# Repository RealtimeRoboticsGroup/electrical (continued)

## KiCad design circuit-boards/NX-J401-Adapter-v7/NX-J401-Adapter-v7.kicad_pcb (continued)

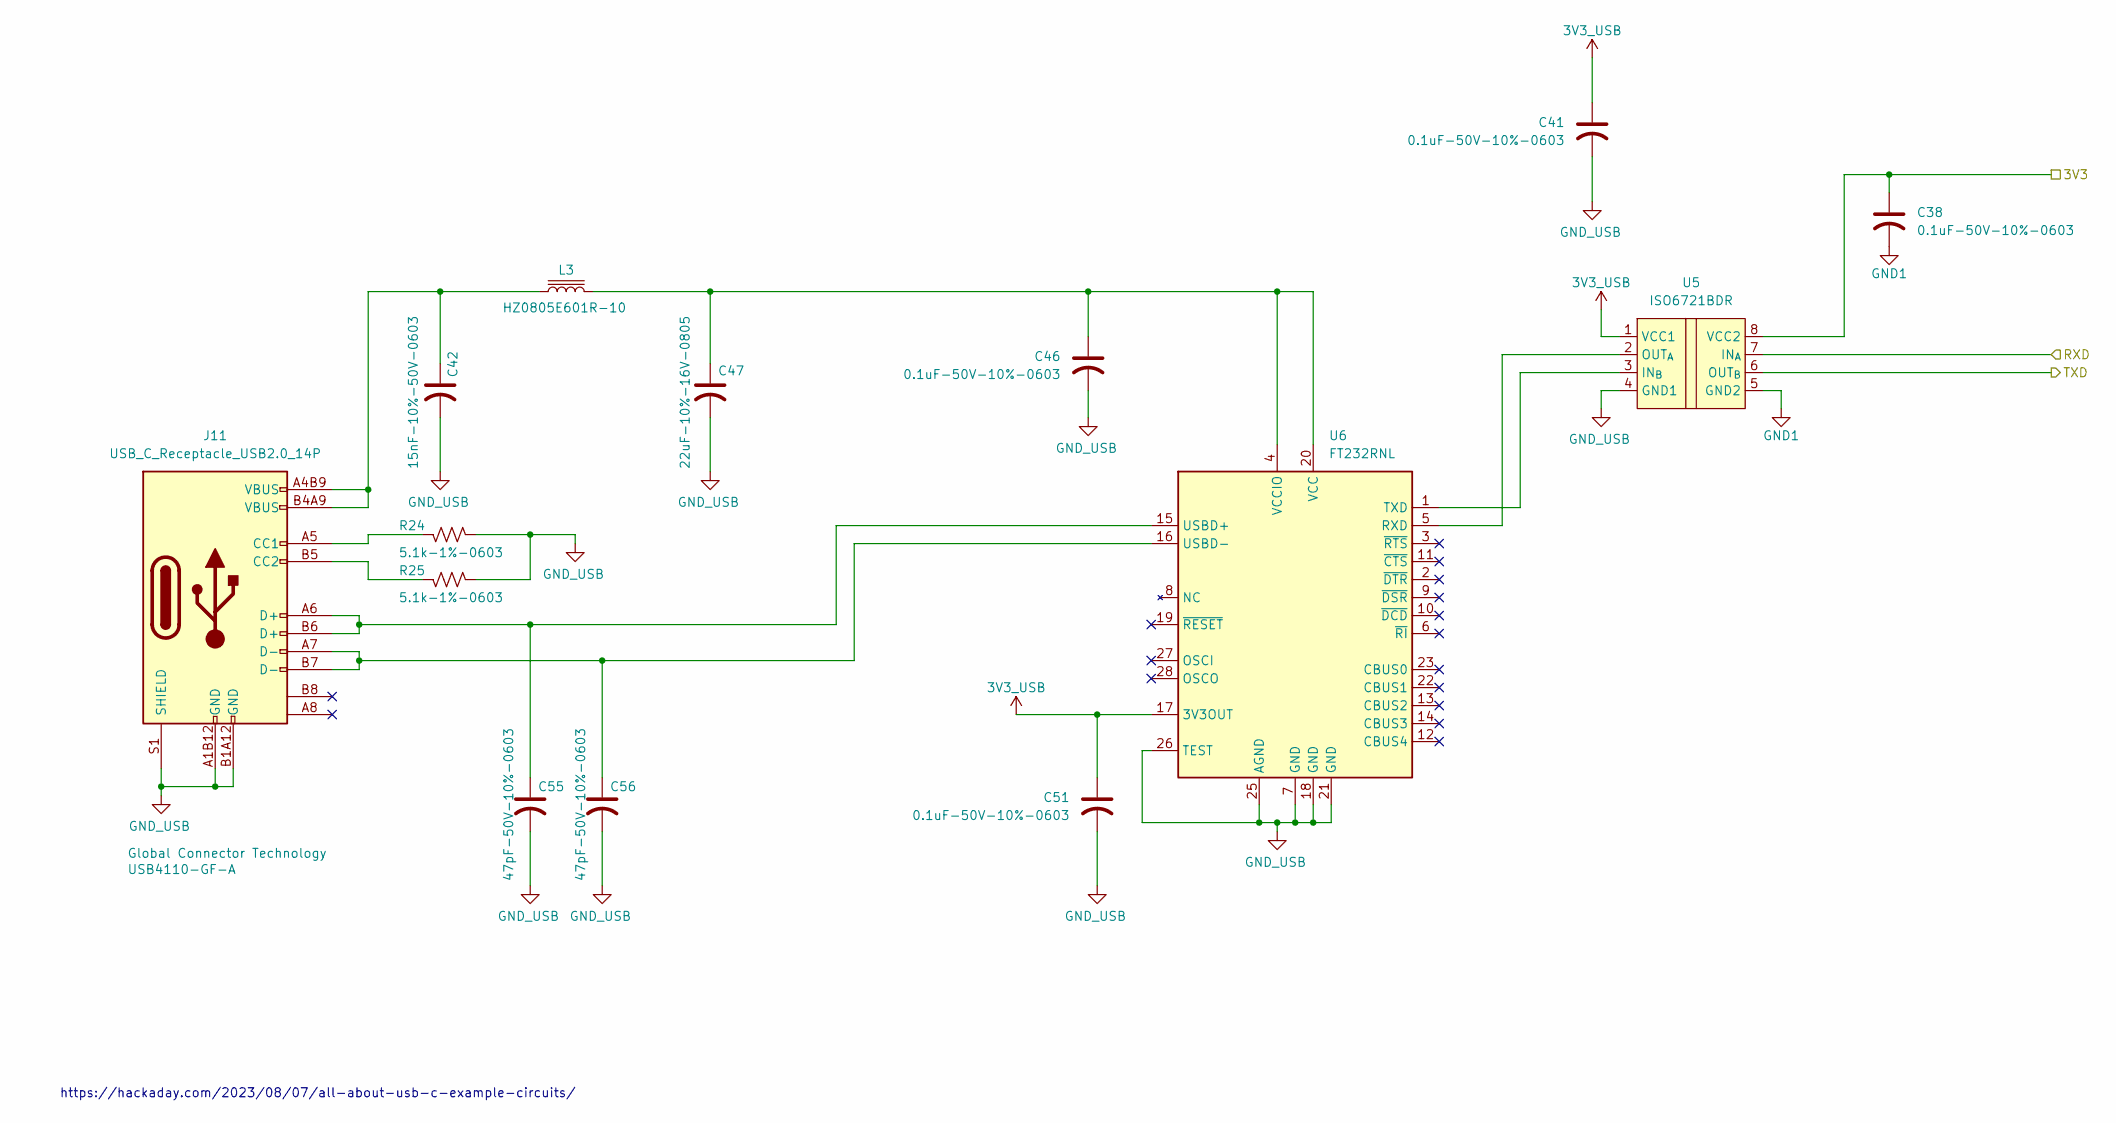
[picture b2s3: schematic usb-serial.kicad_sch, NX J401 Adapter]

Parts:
C38, C41, C46, C51: 0.1uF-50V-10%-0603; C_0603_1608Metric; MFG P/N CC0603KRX7R9BB104; JLCPCB P/N C14663
C42: 15nF-10%-50V-0603; C_0603_1608Metric; MFG P/N CC0603KRX7R9BB153; JLCPCB P/N C107076
C47: 22uF-10%-16V-0805; C_0805_2012Metric; MFG P/N CL21A226KOQNNNE; JLCPCB P/N C296720
C55, C56: 47pF-50V-10%-0603; C_0603_1608Metric; MFG P/N C0603C470K5GACAUTO; JLCPCB P/N C2168903
J11: USB_C_Receptacle_USB2.0_14P; GCT-USB-C-USB4110-GF-A; MFG P/N USB4110-GF-A; JLCPCB P/N C5143397
L3: HZ0805E601R-10; L_0805_2012Metric; MFG P/N HZ0805E601R-10; JLCPCB P/N C2441364
R24, R25: 5.1k-1%-0603; R_0603_1608Metric; MFG P/N RC0603FR-075K1L; JLCPCB P/N C105580
U5: ISO6721BDR; SOIC-8_3.9x4.9mm_P1.27mm; MFG P/N ISO6721BDR; JLCPCB P/N C5216430
U6: FT232RNL; SSOP-28_5.3x10.2mm_P0.65mm; MFG P/N FT232RNL; JLCPCB P/N C8690

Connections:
3V3_USB: C41.1, C51.1, U5.1 (VCC1), U6.17 (3V3OUT)
/3V3_BTN: C38.1, U5.8 (VCC2); also elsewhere on the board
/UART2_RXD: U5.7 (IN_{A}); also elsewhere on the board
/UART2_TXD: U5.6 (OUT_{B}); also elsewhere on the board
GND1: C38.2, U5.5 (GND2); also elsewhere on the board
GND_USB: C41.2, C42.2, C46.2, C47.2, C51.2, C55.2, C56.2, J11.A1B12 (GND), J11.B1A12 (GND), J11.S1 (SHIELD), R24.2, R25.2, U5.4 (GND1), U6.7 (GND), U6.18 (GND), U6.21 (GND), U6.25 (AGND), U6.26 (TEST)
unnamed: C42.1, J11.A4B9 (VBUS), J11.B4A9 (VBUS), L3.1
unnamed: J11.A5 (CC1), R24.1
unnamed: J11.B5 (CC2), R25.1
unnamed: U5.3 (IN_{B}), U6.1 (TXD)
unnamed: U5.2 (OUT_{A}), U6.5 (RXD)
unnamed: C55.1, J11.A6 (D+), J11.B6 (D+), U6.15 (USBD+)
unnamed: C56.1, J11.A7 (D-), J11.B7 (D-), U6.16 (USBD-)
unnamed: C46.1, C47.1, L3.2, U6.4 (VCCIO), U6.20 (VCC)

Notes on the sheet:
https://hackaday.com/2023/08/07/all-about-usb-c-example-circuits/

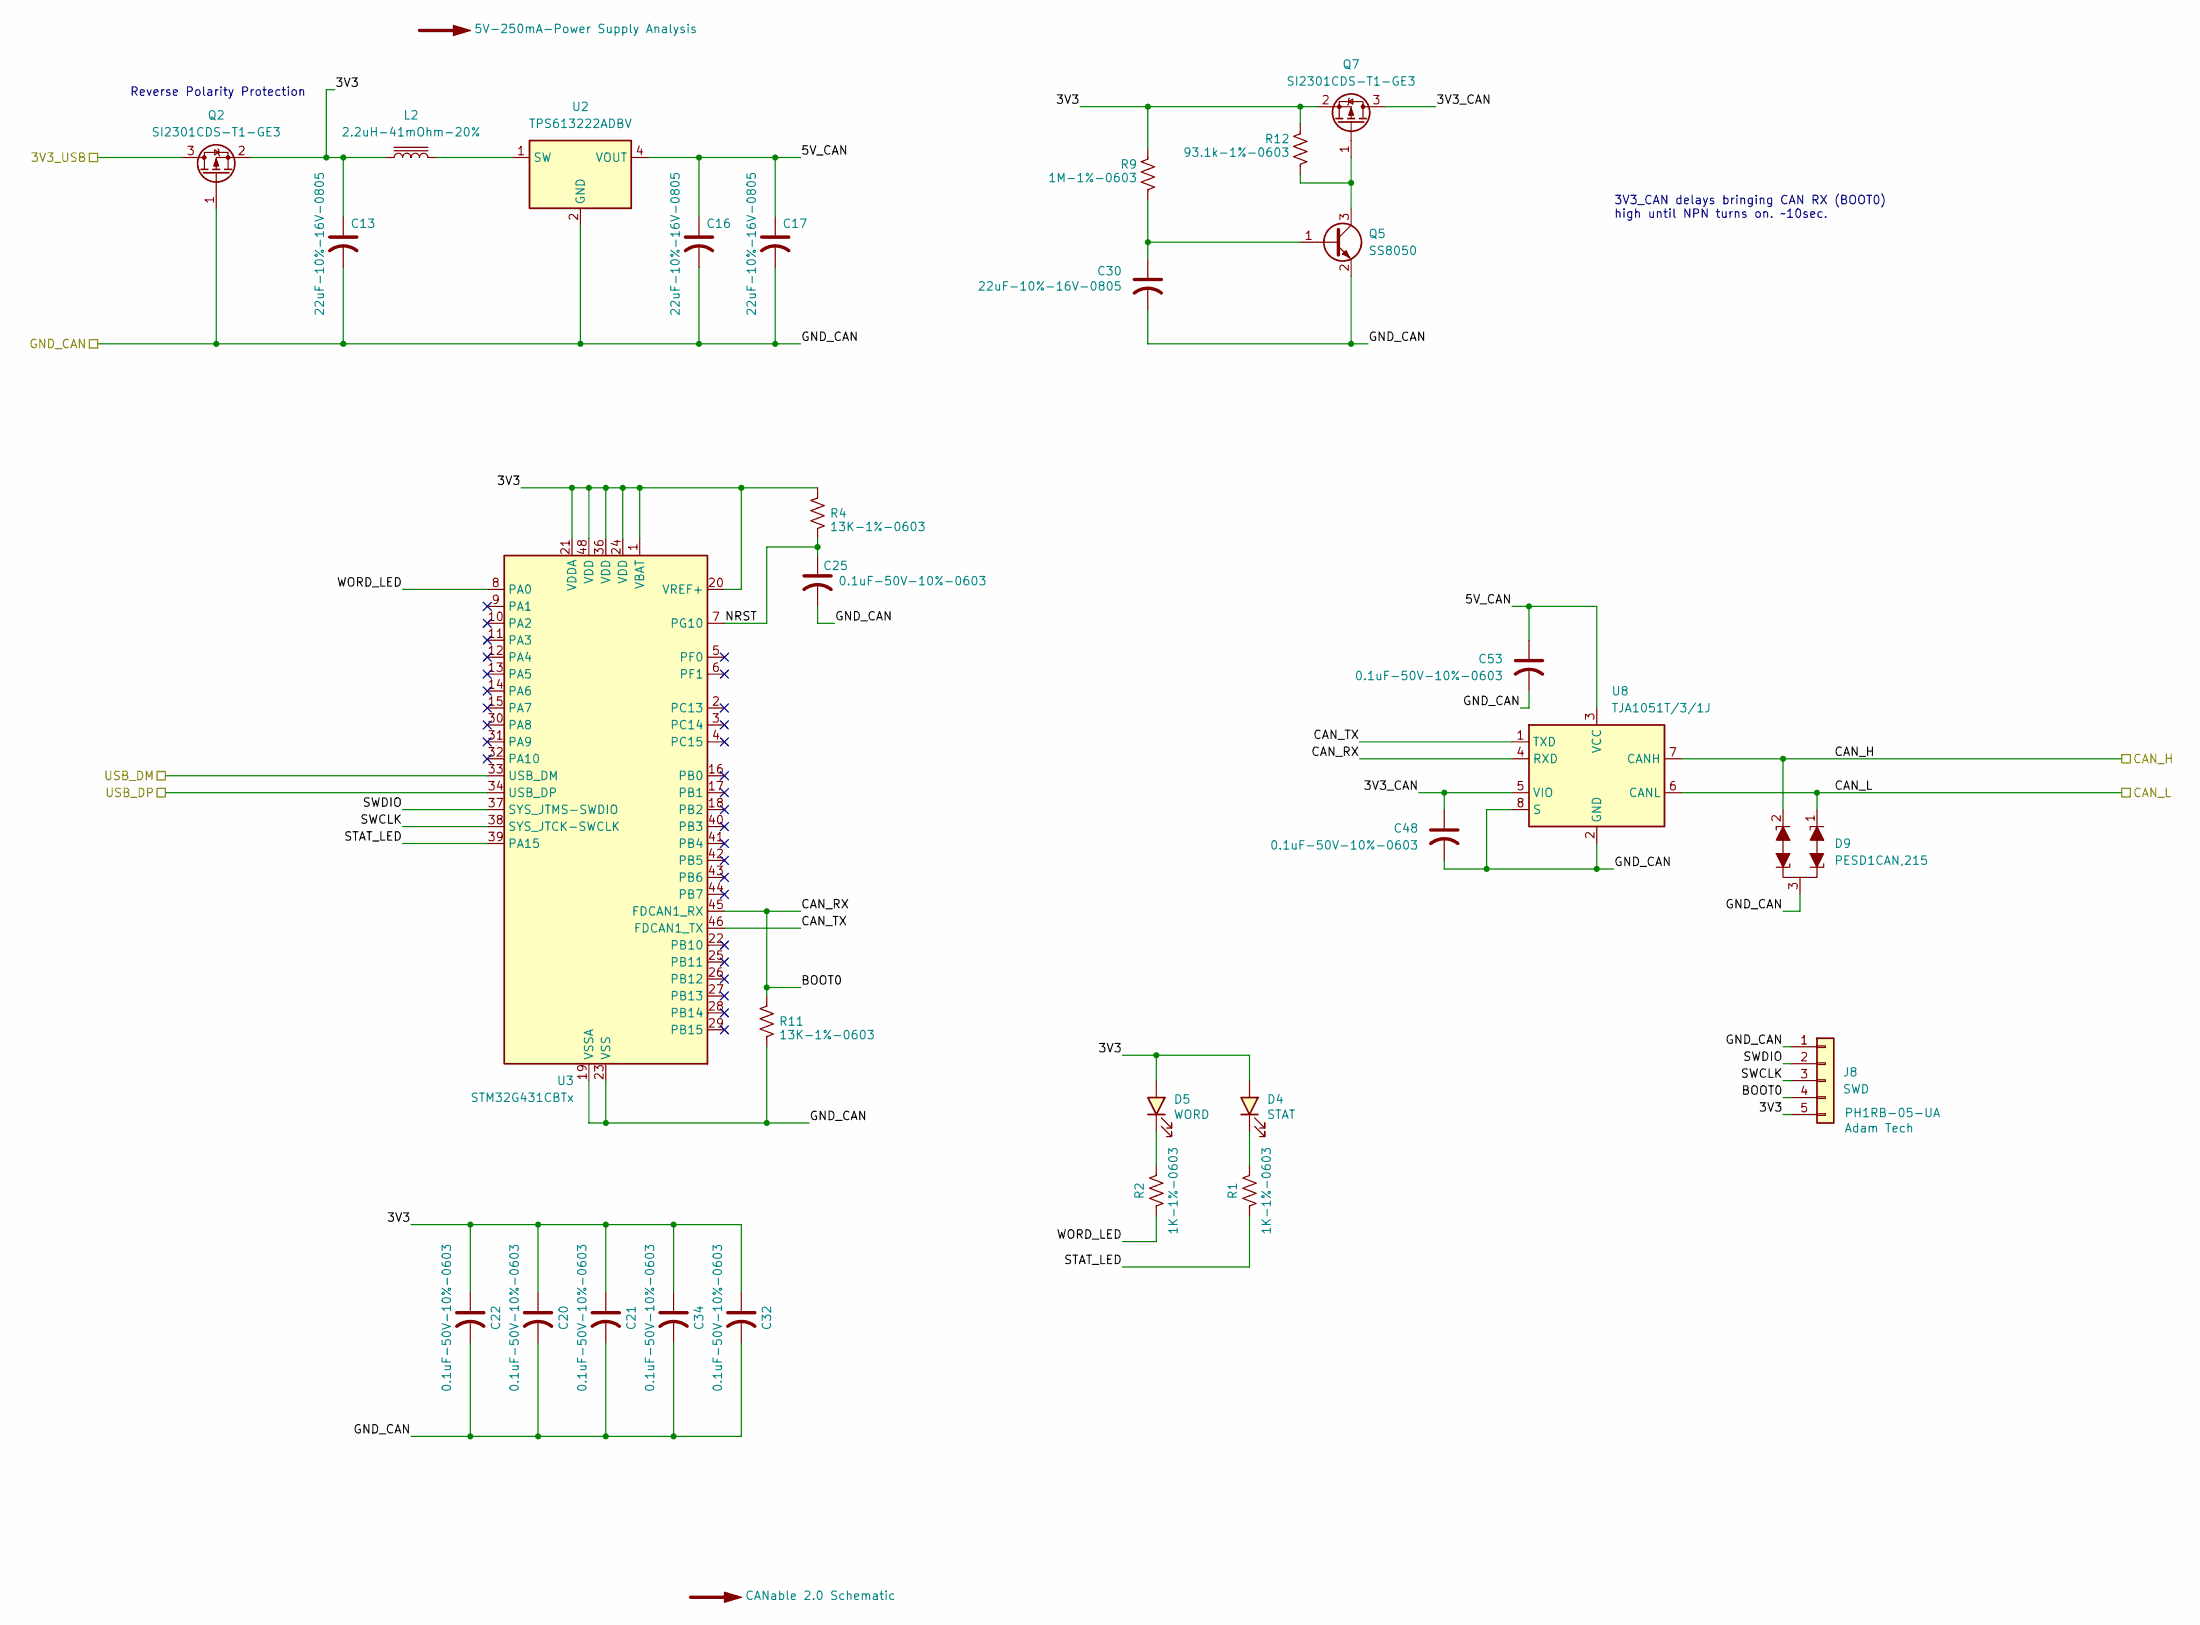
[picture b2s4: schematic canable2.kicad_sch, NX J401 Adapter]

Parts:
C13, C16, C17, C30: 22uF-10%-16V-0805; C_0805_2012Metric; MFG P/N CL21A226KOQNNNE; JLCPCB P/N C296720
C20, C21, C22, C25, C32, C34, C48, C53: 0.1uF-50V-10%-0603; C_0603_1608Metric; MFG P/N CC0603KRX7R9BB104; JLCPCB P/N C14663
D4: STAT; LED_1206_3216Metric; MFG P/N XL-3216UYC; JLCPCB P/N C965824
D5: WORD; LED_1206_3216Metric; MFG P/N XL-3216UYC; JLCPCB P/N C965824
D9: PESD1CAN; SOT-23; MFG P/N PESD1CAN,215; JLCPCB P/N C15771
J8: SWD; PinHeader_1x05_P2.54mm_Horizontal; MFG P/N PH1RB-05-UA; JLCPCB P/N XXXXXX
L2: 2.2uH-41mOhm-20%; KOHER-MDA4020-2R2M; MFG P/N MDA4020-2R2M; JLCPCB P/N C2847469
Q2, Q7: SI2301CDS-T1-GE3; SOT-23; MFG P/N SI2301CDS-T1-GE3; JLCPCB P/N C10487
Q5: SS8050; SOT-23; MFG P/N SS8050(RANGE:200-350); JLCPCB P/N C2150
R1, R2: 1K-1%-0603; R_0603_1608Metric; MFG P/N RC0603FR-071KL; JLCPCB P/N C22548
R4, R11: 13K-1%-0603; R_0603_1608Metric; MFG P/N RC0603FR-0713KL; JLCPCB P/N C137796
R9: 1M-1%-0603; R_0603_1608Metric; MFG P/N RC0603FR-071ML; JLCPCB P/N C105578
R12: 93.1k-1%-0603; R_0603_1608Metric; MFG P/N AC0603FR-0793K1L; JLCPCB P/N C228101
U2: TPS613222ADBV; SOT-23-5; MFG P/N TPS613222ADBVR; JLCPCB P/N C2071163
U3: STM32G431CBTx; LQFP-48_7x7mm_P0.5mm; MFG P/N STM32G431CBT6; JLCPCB P/N C529355
U8: TJA1051T/3/1J; SO-8_3.9x4.9mm_P1.27mm; MFG P/N TJA1051T/3/1J; JLCPCB P/N C38695

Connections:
/CANable2.0/3V3: C13.1, C20.1, C21.1, C22.1, C32.1, C34.1, D4.2 (A), D5.2 (A), J8.5, L2.1, Q2.2 (S), Q7.2 (S), R4.1, R9.1, R12.1, U3.1 (VBAT), U3.20 (VREF+), U3.21 (VDDA), U3.24 (VDD), U3.36 (VDD), U3.48 (VDD)
/CANable2.0/3V3_CAN: C48.1, Q7.3 (D), U8.5 (VIO)
/CANable2.0/3V3_USB: Q2.3 (D); also elsewhere on the board
/CANable2.0/5V_CAN: C16.1, C17.1, C53.1, U2.4 (VOUT), U8.3 (VCC)
/CANable2.0/BOOT0: J8.4, R11.1, U3.45 (FDCAN1_RX), U8.4 (RXD)
/CANable2.0/CAN_H: D9.2 (K1), U8.7 (CANH); also elsewhere on the board
/CANable2.0/CAN_L: D9.1 (K1), U8.6 (CANL); also elsewhere on the board
/CANable2.0/CAN_TX: U3.46 (FDCAN1_TX), U8.1 (TXD)
/CANable2.0/GND_CAN: C13.2, C16.2, C17.2, C20.2, C21.2, C22.2, C25.2, C30.2, C32.2, C34.2, C48.2, C53.2, D9.3 (KK), J8.1, Q2.1 (G), Q5.2 (E), R11.2, U2.2 (GND), U3.19 (VSSA), U3.23 (VSS), U3.35 (VSS), U3.47 (VSS), U8.2 (GND), U8.8 (S); also elsewhere on the board
/CANable2.0/NRST: C25.1, R4.2, U3.7 (PG10)
/CANable2.0/STAT_LED: R1.2, U3.39 (PA15)
/CANable2.0/SWCLK: J8.3, U3.38 (SYS_JTCK-SWCLK)
/CANable2.0/SWDIO: J8.2, U3.37 (SYS_JTMS-SWDIO)
/CANable2.0/USB_DM: U3.33 (USB_DM); also elsewhere on the board
/CANable2.0/USB_DP: U3.34 (USB_DP); also elsewhere on the board
/CANable2.0/WORD_LED: R2.2, U3.8 (PA0)
unnamed: D4.1 (K), R1.1
unnamed: D5.1 (K), R2.1
unnamed: C30.1, Q5.1 (B), R9.2
unnamed: Q5.3 (C), Q7.1 (G), R12.2
unnamed: L2.2, U2.1 (SW)

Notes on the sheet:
3V3_CAN delays bringing CAN RX (BOOT0) high until NPN turns on. ~10sec.
Reverse Polarity Protection

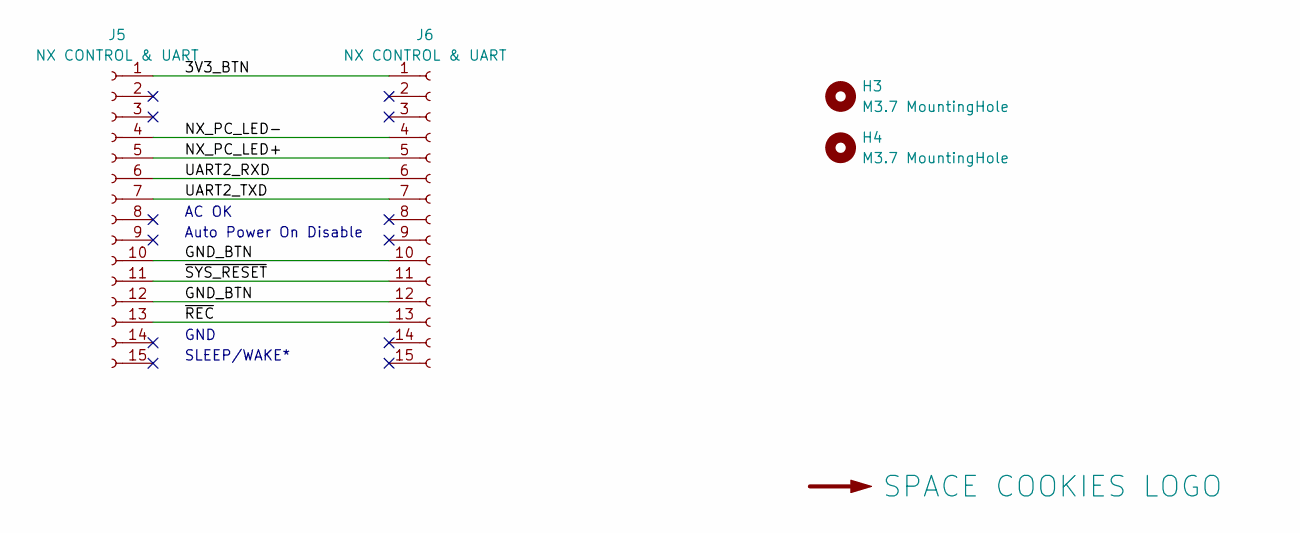
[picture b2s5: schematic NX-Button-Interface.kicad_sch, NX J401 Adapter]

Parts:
H3, H4: M3.7 MountingHole; MountingHole_3.7mm
J5, J6: NX CONTROL & UART; PinSocket_1x15_P2.54mm_Vertical; MFG P/N PPTC151LFBN-RC; JLCPCB P/N XXXXXX
LOGO2: SPACE COOKIES LOGO; SPACE_COOKIES_LOGO_7mm

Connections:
/NX-Button Interface/3V3_BTN: J5.1, J6.1
/NX-Button Interface/GND_BTN: J5.10, J5.12, J6.10, J6.12
/NX-Button Interface/NX_PC_LED+: J5.5, J6.5
/NX-Button Interface/NX_PC_LED-: J5.4, J6.4
/NX-Button Interface/UART2_RXD: J5.6, J6.6
/NX-Button Interface/UART2_TXD: J5.7, J6.7
/NX-Button Interface/~REC: J5.13, J6.13
/NX-Button Interface/~SYS_RESET: J5.11, J6.11

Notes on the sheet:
AC OK
GND
Auto Power On Disable
SLEEP/WAKE*

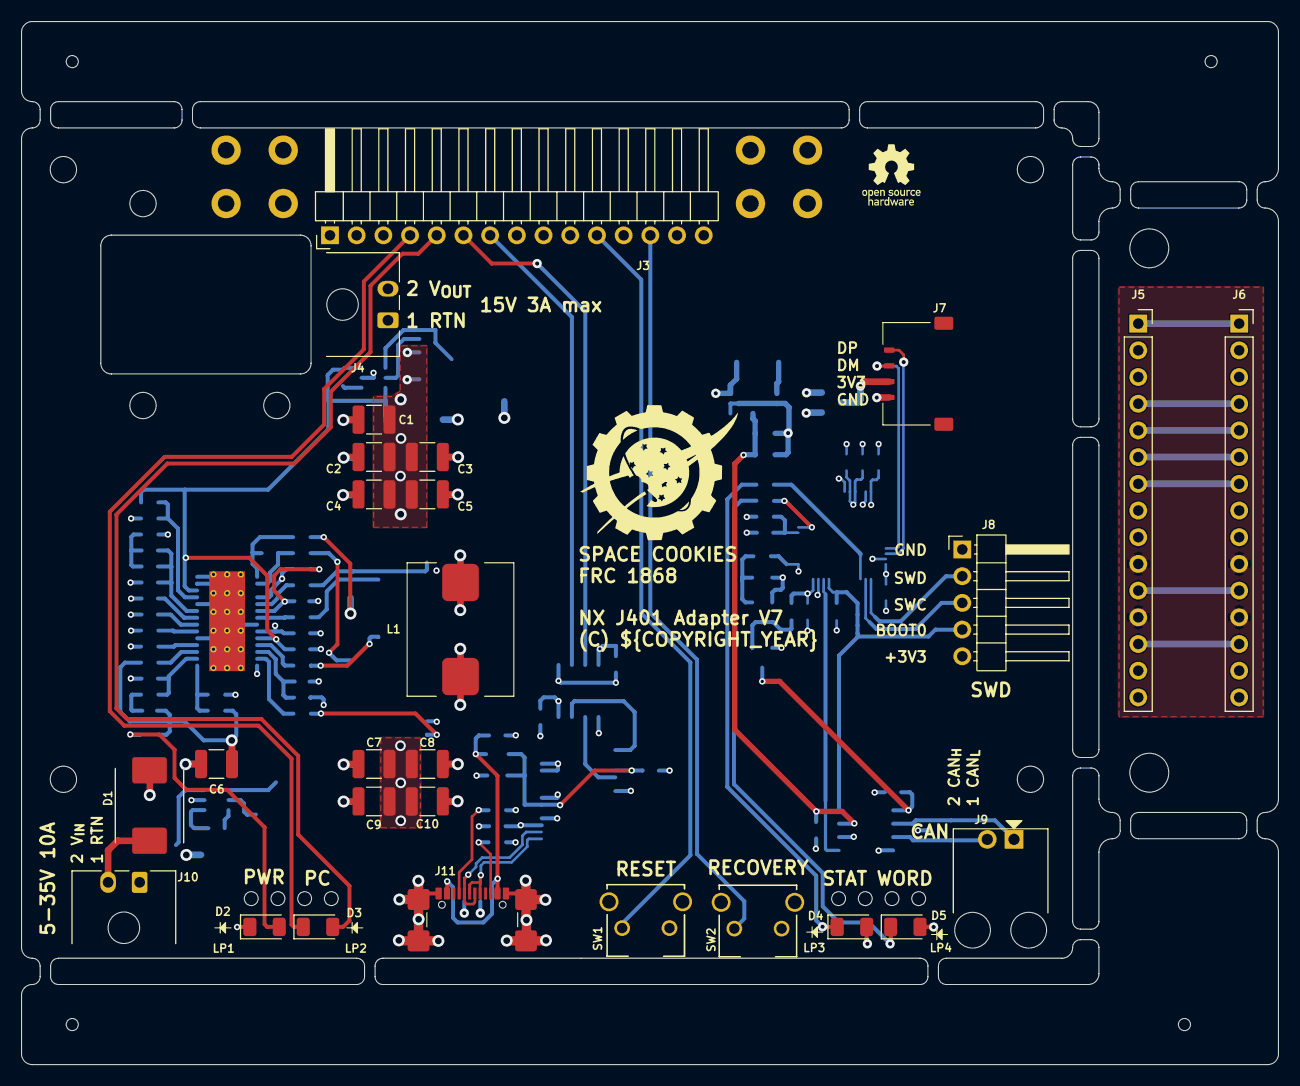
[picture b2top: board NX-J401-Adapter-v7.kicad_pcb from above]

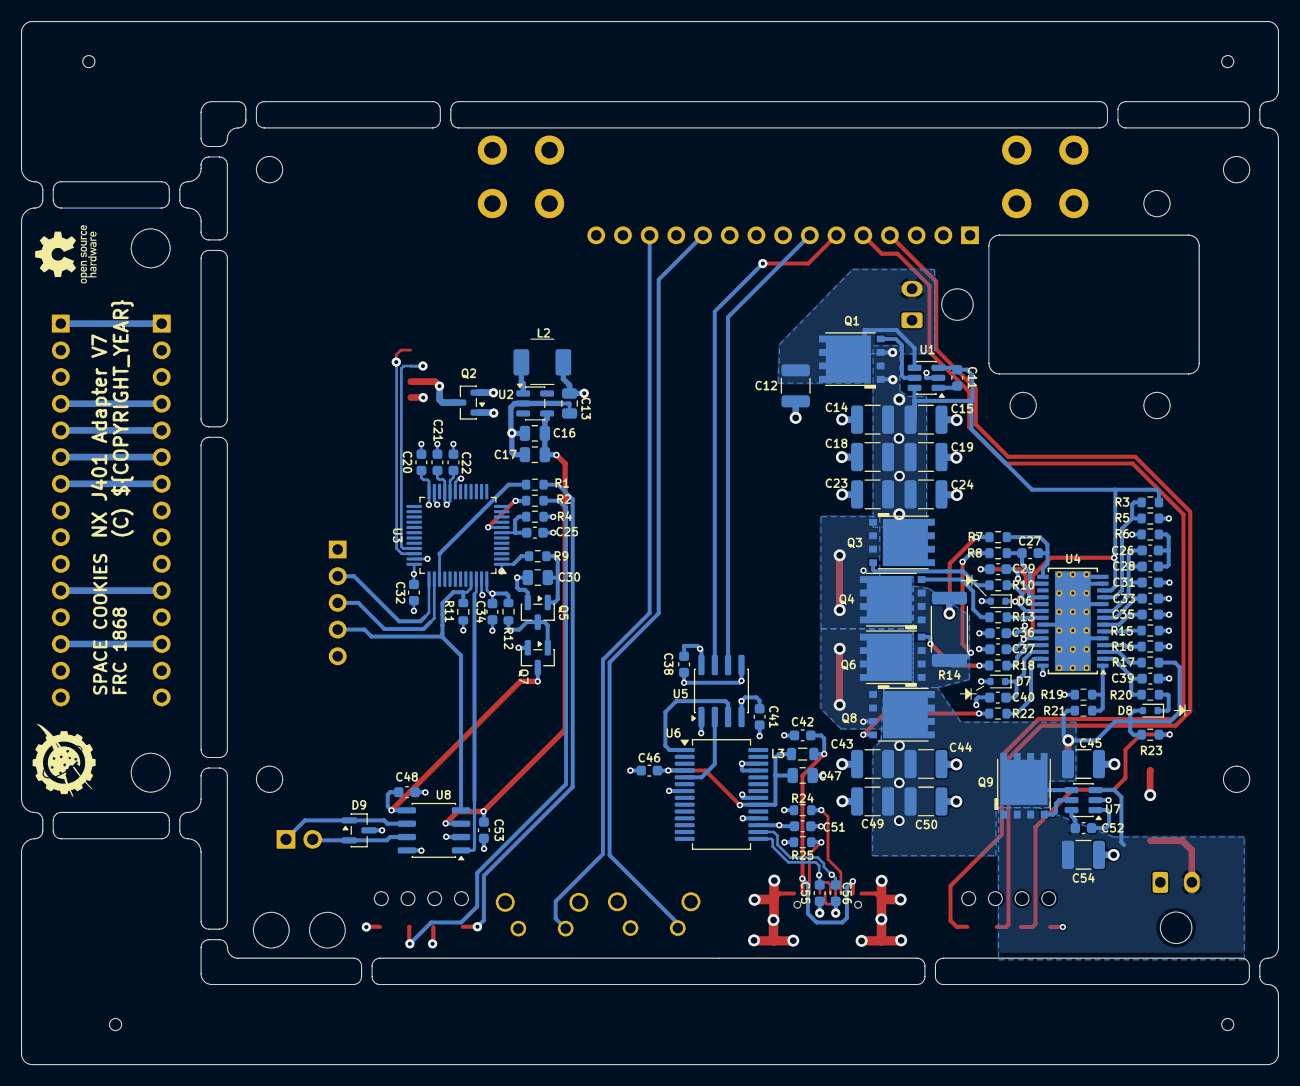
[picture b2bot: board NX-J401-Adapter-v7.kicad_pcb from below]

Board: 4 copper layers, 119.6 x 99.2 mm, 142 parts (95 on the bottom side), 84 nets.

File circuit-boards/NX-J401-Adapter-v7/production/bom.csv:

Designator,Footprint,Quantity,Value,LCSC Part #
"C1, C10, C12, C14, C15, C18, C19, C2, C23, C24, C3, C4, C43, C44, C45, C49, C5, C50, C54, C6, C7, C8, C9",1210,23,10uF-50V-10%-X7R-1210,C77102
"C11, C20, C21, C22, C25, C29, C32, C34, C37, C38, C39, C40, C41, C46, C48, C51, C52, C53",0603,18,0.1uF-50V-10%-0603,C14663
"C13, C16, C17, C30, C47",0805,5,22uF-10%-16V-0805,C296720
"C26, C28",0603,2,5.6nF-10%-50V-0603,C107095
"C27, C55, C56",0603,3,47pF-50V-10%-0603,C2168903
C31,0603,1,270pF-10%-50V-0603,C107084
"C33, C42",0603,2,15nF-10%-50V-0603,C107076
C35,0603,1,150pF-50V-10%-0603,C107075
C36,0603,1,1uF-50V-10%-0603,C105174
D1,D_SMC_Littelfuse_DO-214AB,1,24V,C284061
D2,1206,1,PWR,C5123493
D3,1206,1,PC,C5123493
D4,1206,1,STAT,C965824
D5,1206,1,WORD,C965824
"D6, D7, D8",D_SOD-523,3,BAT54KFILM,C283259
D9,SOT-23,1,PESD1CAN,C15771
"J1, J2",Keystone-7774,2,Terminal,XXXXXX
J10,Molex_Micro-Fit_3.0_43650-0200_1x02_P3.00mm_Horizontal,1,POWER,XXXXXX
J11,GCT-USB-C-USB4110-GF-A,1,USB_C_Receptacle_USB2.0_14P,C5143397
J3,PinHeader_1x15_P2.54mm_Horizontal,1,NX CONTROL & UART,XXXXXX
J4,Molex_Micro-Fit_3.0_43650-0200_1x02_P3.00mm_Horizontal,1,15V,XXXXXX
"J5, J6",PinSocket_1x15_P2.54mm_Vertical,2,NX CONTROL & UART,XXXXXX
J7,Molex-PicoLatch-5040500491,1,USB1,C177235
J8,PinHeader_1x05_P2.54mm_Horizontal,1,SWD,XXXXXX
J9,Molex-70555-0001,1,CAN1,XXXXXX
L1,Koher-MDA1050,1,2.2uH-19A-5.1mohm-20%,C2847559
L2,KOHER-MDA4020-2R2M,1,2.2uH-41mOhm-20%,C2847469
L3,0805,1,HZ0805E601R-10,C2441364
"LP1, LP2, LP3, LP4",Bivar-SLP3-150-100-F,4,Light Pipe,XXXXXX
"Q1, Q6, Q8, Q9",TI-SON5x6,4,CSD19534Q5A,C114200
"Q2, Q7",SOT-23,2,SI2301CDS-T1-GE3,C10487
"Q3, Q4",TI-SON5x6,2,CSD17578Q5A,C2871447
Q5,SOT-23,1,SS8050,C2150
"R1, R2",0603,2,1K-1%-0603,C22548
"R10, R13, R18, R22",0603,4,0R-1%-0603,C100044
"R11, R15, R4",0603,3,13K-1%-0603,C137796
"R12, R19",0603,2,93.1k-1%-0603,C228101
R14,2512,1,10mOhm-3W-1%-2512,C723413
R16,0603,1,205K-1%-0603,C22949
"R17, R23",0603,2,2K-1%-0603,C105576
R20,0603,1,10R0-1%-0603,C109318
R21,0603,1,249K-1%-0603,C706146
"R24, R25",0603,2,5.1k-1%-0603,C105580
R3,0603,1,357K-1%-0603,C227834
R5,0603,1,20K-1%-0603,C105575
R6,0603,1,5.9k-1%-0603,C23071
"R7, R8",0603,2,100R-1%-0603,C105588
R9,0603,1,1M-1%-0603,C105578
SW1,SW_TL1105VF100Q_EWI,1,RESET,XXXXXX
SW2,SW_TL1105VF100Q_EWI,1,RECOVERY,XXXXXX
"U1, U7",SOT-23-6,2,LM74700QDBVRQ1,C2941042
U2,SOT-23-5,1,TPS613222ADBV,C2071163
U3,LQFP-48_7x7mm_P0.5mm,1,STM32G431CBTx,C529355
U4,HTSSOP-28-1EP_4.4x9.7mm_P0.65mm_EP3.4x9.5mm_ThermalVias,1,LM5176PWPR,C442493
U5,SOIC-8_3.9x4.9mm_P1.27mm,1,ISO6721BDR,C5216430
U6,SSOP-28_5.3x10.2mm_P0.65mm,1,FT232RNL,C8690
U8,SO-8_3.9x4.9mm_P1.27mm,1,TJA1051T/3/1J,C38695

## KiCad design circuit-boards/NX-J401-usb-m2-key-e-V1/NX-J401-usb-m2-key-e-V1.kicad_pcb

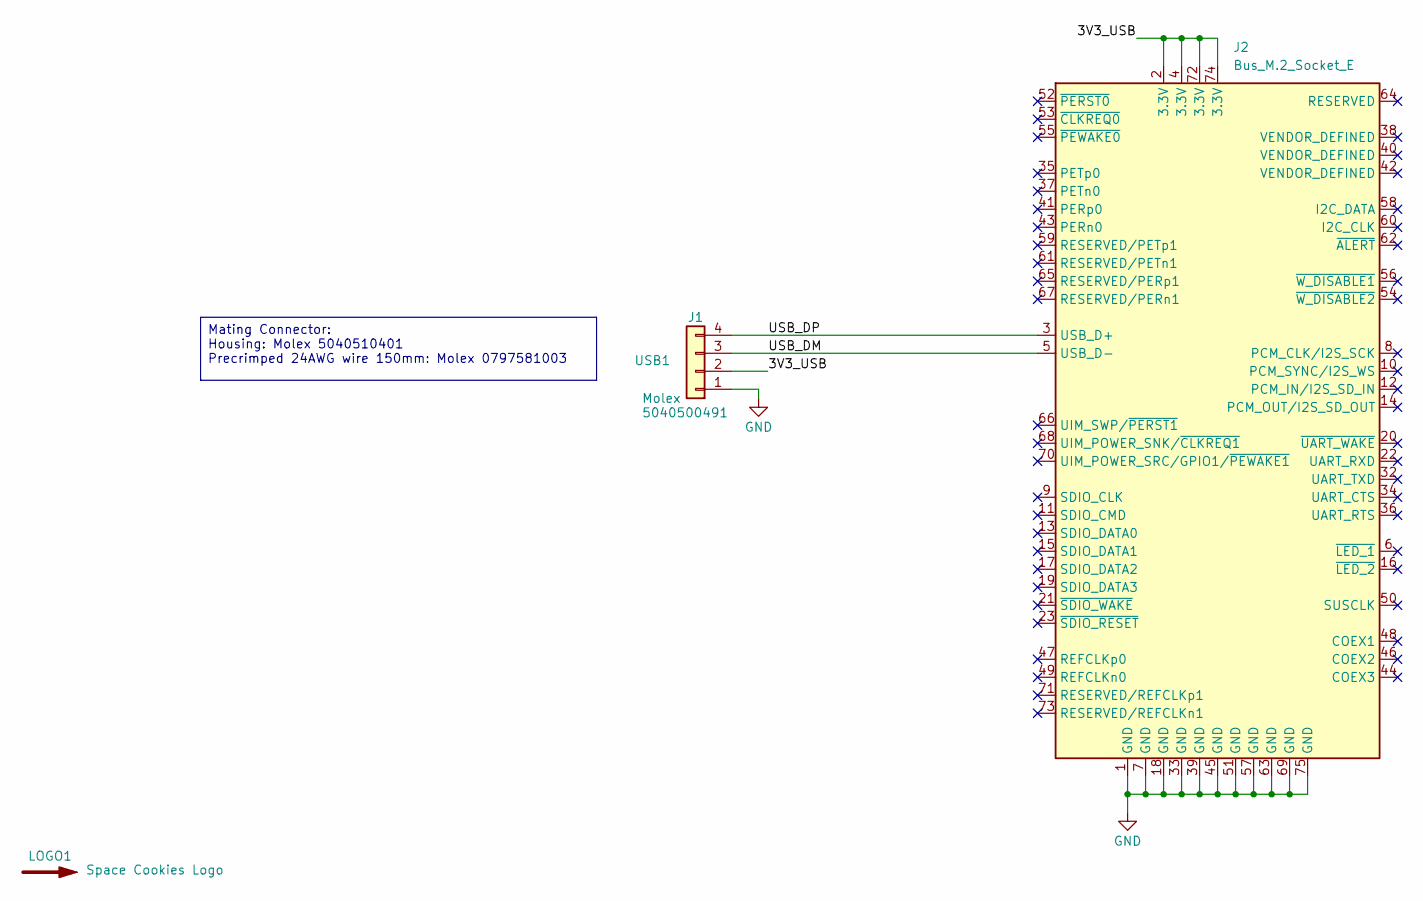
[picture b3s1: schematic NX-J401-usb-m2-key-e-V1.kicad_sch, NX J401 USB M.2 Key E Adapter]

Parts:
J1: USB1; Molex-PicoLatch-5040500491; MFG P/N 5040500491; JLCPCB P/N C177235
J2: Bus_M.2_Socket_E; M.2_2230-xx-E
LOGO1: Space Cookies Logo; SPACE_COOKIES_LOGO_7mm

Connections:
/3V3_USB: J1.2, J2.2 (3.3V), J2.4 (3.3V), J2.72 (3.3V), J2.74 (3.3V)
/USB_DM: J1.3, J2.5 (USB_D-)
/USB_DP: J1.4, J2.3 (USB_D+)
GND: J1.1, J2.1 (GND), J2.7 (GND), J2.18 (GND), J2.33 (GND), J2.39 (GND), J2.45 (GND), J2.51 (GND), J2.57 (GND), J2.63 (GND), J2.69 (GND), J2.75 (GND)

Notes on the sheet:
Mating Connector: Housing: Molex 5040510401 Precrimped 24AWG wire 150mm: Molex 0797581003

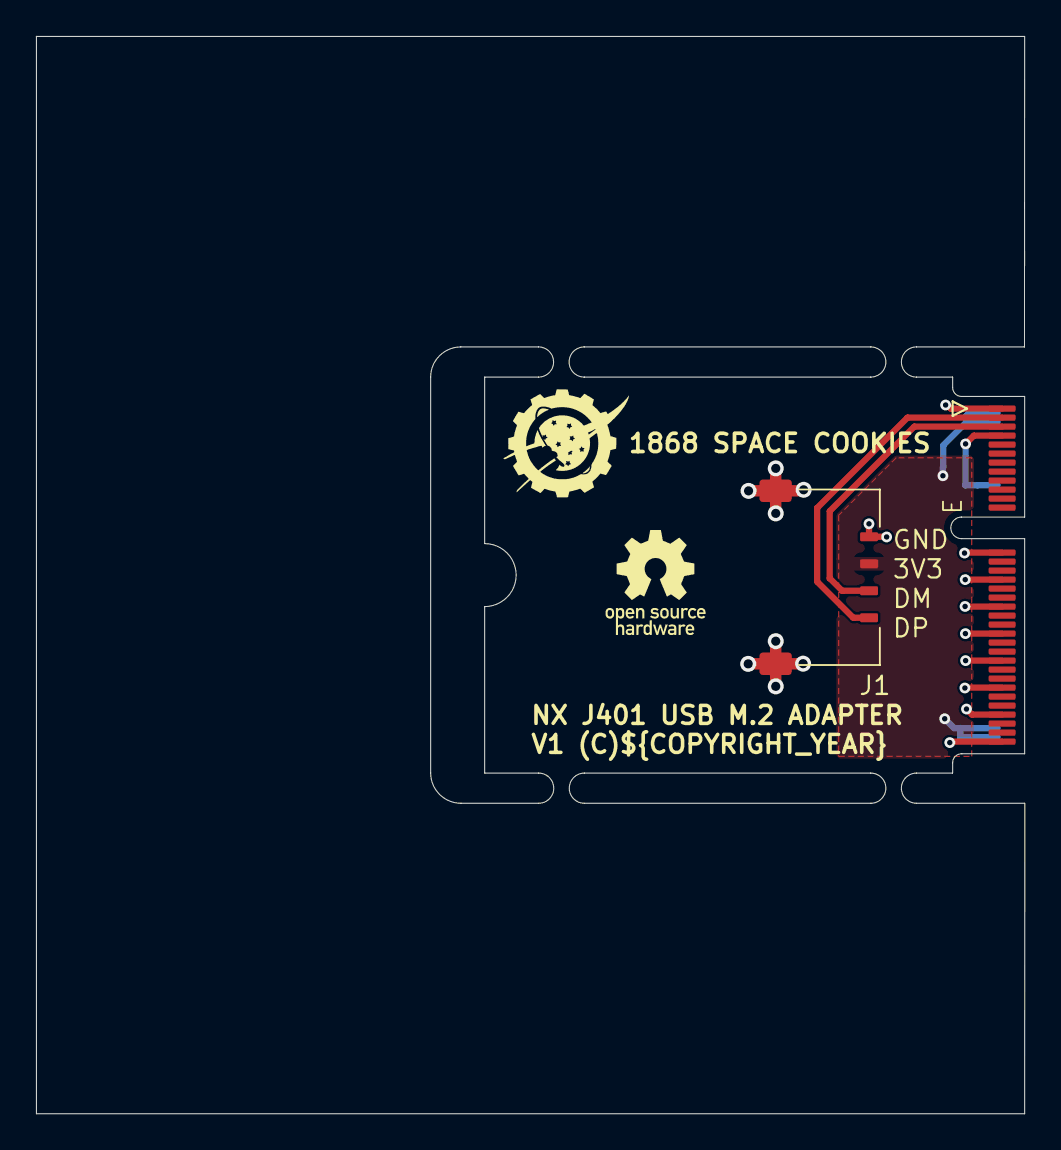
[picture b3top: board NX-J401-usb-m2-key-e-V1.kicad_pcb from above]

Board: 2 copper layers, 54.9 x 59.8 mm, 3 parts (0 on the bottom side), 4 nets.

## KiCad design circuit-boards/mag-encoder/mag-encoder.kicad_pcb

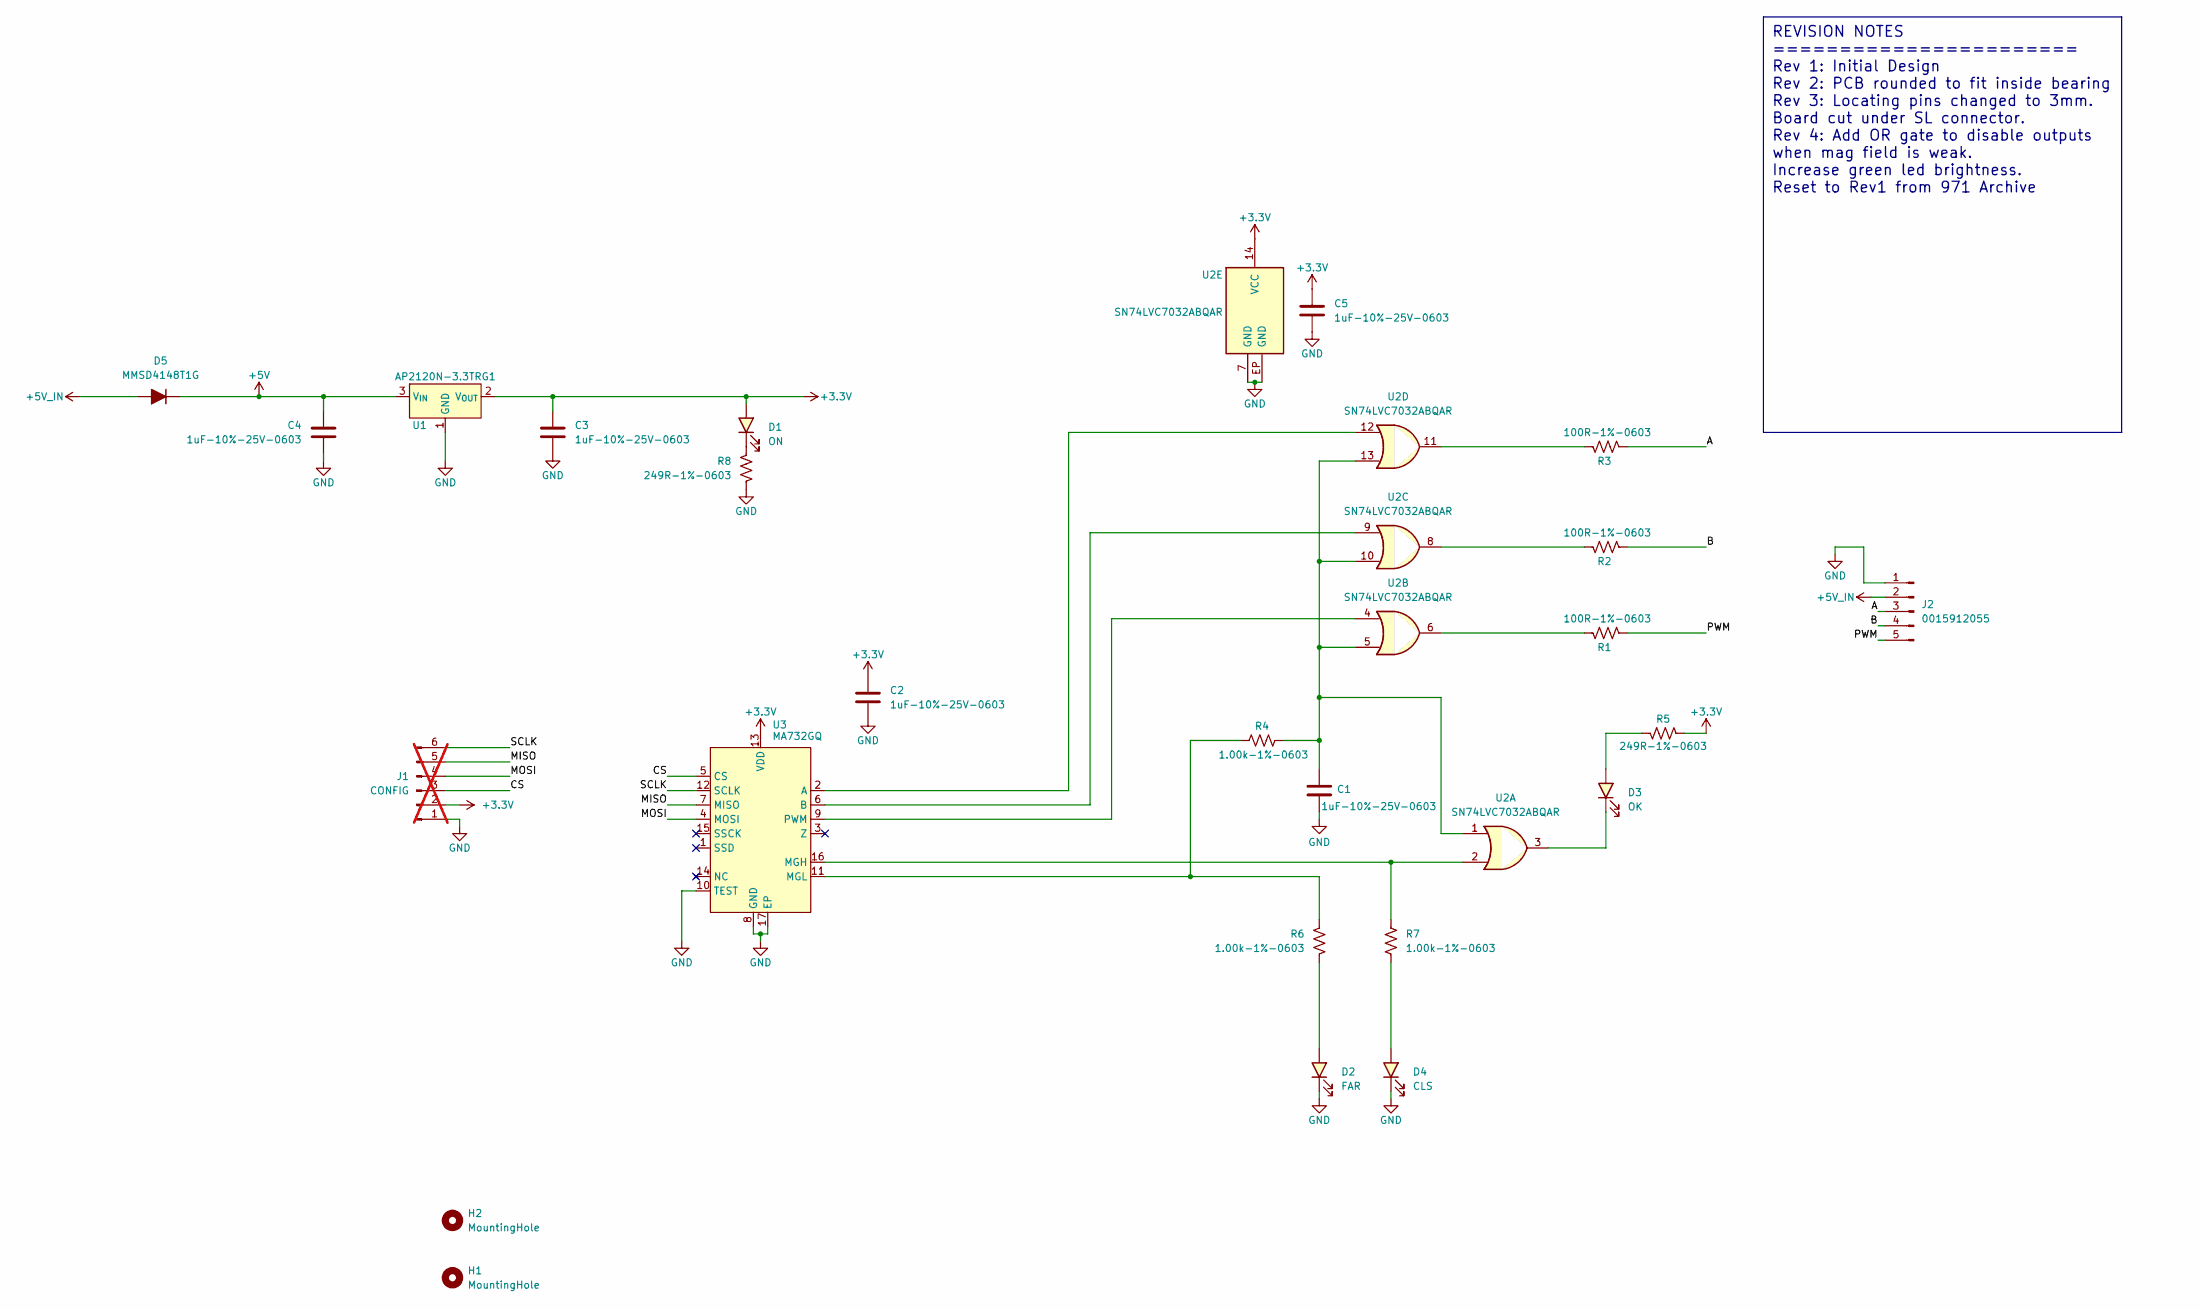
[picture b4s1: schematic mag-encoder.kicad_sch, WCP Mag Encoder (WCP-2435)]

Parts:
C1, C2, C3, C4, C5: 1uF-10%-25V-0603; C_0603_1608Metric; MFG P/N 06033C105KAT2A
D1: ON; LED_0603_1608Metric; MFG P/N 150060VS75000
D2: FAR; LED_0603_1608Metric; MFG P/N 150060RS75000
D3: OK; LED_0603_1608Metric; MFG P/N 150060VS75000
D4: CLS; LED_0603_1608Metric; MFG P/N 150060YS75000
D5: MMSD4148T1G; D_SOD-123; MFG P/N MMSD4148T1G
H1, H2: MountingHole; pin-0.100
J1: CONFIG; PinHeader_1x06_P2.54mm_Vertical; not fitted
J2: 0015912055; Molex-70634-0039; MFG P/N 0015912055
R1, R2, R3: 100R-1%-0603; R_0603_1608Metric; MFG P/N RC0603FR-07100RL
R4, R6, R7: 1.00k-1%-0603; R_0603_1608Metric; MFG P/N RC0603FR-071KL
R5, R8: 249R-1%-0603; R_0603_1608Metric; MFG P/N RC0603FR-07249RL
U1: AP2120N-3.3TRG1; SOT-23; MFG P/N AP2120N-3.3TRG1
U2: SN74LVC7032ABQAR; TI-WQFN-14-1EP_2.5x3mm_EP_1x1.5mm; MFG P/N SN74LVC7032ABQAR
U3: MA732GQ; QFN-16-1EP_3x3mm_P0.5mm_EP1.7x1.7mm; MFG P/N MA732GQ-Z

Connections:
+3.3V: C2.1, C3.1, C5.1, D1.2 (A), J1.2, R5.1, U1.2 (V_{OUT}), U2.14 (VCC), U3.13 (VDD)
+5V: C4.1, D5.1 (K), U1.3 (V_{IN})
+5V_IN: D5.2 (A), J2.2
/A: J2.3, R3.2
/B: J2.4, R2.2
/CS: J1.3, U3.5 (CS)
/MISO: J1.5, U3.7 (MISO)
/MOSI: J1.4, U3.4 (MOSI)
/PWM: J2.5, R1.2
/SCLK: J1.6, U3.12 (SCLK)
GND: C1.2, C2.2, C3.2, C4.2, C5.2, D2.1 (K), D4.1 (K), J1.1, J2.1, R8.2, U1.1 (GND), U2.7 (GND), U2.EP (GND), U3.8 (GND), U3.10 (TEST), U3.17 (EP)
unnamed: C1.1, R4.2, U2.1, U2.5, U2.10, U2.13
unnamed: D1.1 (K), R8.1
unnamed: D2.2 (A), R6.2
unnamed: D3.2 (A), R5.2
unnamed: D3.1 (K), U2.3
unnamed: D4.2 (A), R7.2
unnamed: R1.1, U2.6
unnamed: R2.1, U2.8
unnamed: R3.1, U2.11
unnamed: U2.12, U3.2 (A)
unnamed: U2.9, U3.6 (B)
unnamed: R7.1, U2.2, U3.16 (MGH)
unnamed: R4.1, R6.1, U3.11 (MGL)
unnamed: U2.4, U3.9 (PWM)

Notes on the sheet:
REVISION NOTES ======================= Rev 1: Initial Design Rev 2: PCB rounded to fit inside bearing Rev 3: Locating pins changed to 3mm. Board cut under SL connector. Rev 4: Add OR gate to disable outputs when mag field is weak. Increase green led brightness. Reset to Rev1 from 971 Archive

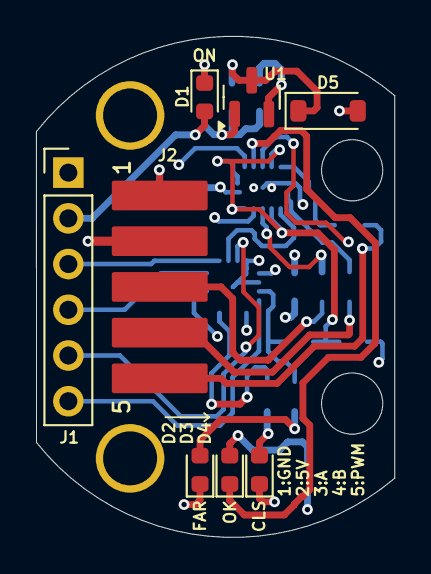
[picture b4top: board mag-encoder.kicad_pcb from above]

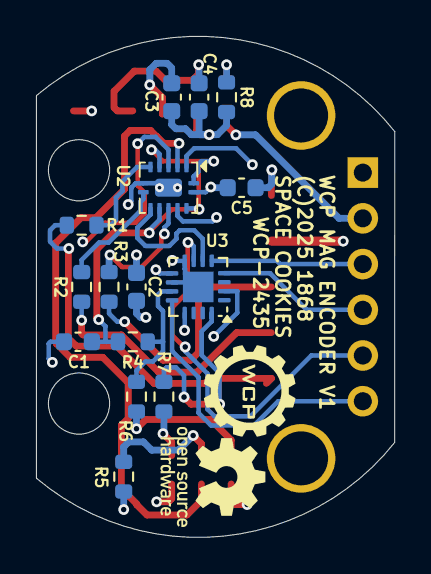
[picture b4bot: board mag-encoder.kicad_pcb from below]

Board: 4 copper layers, 19.9 x 27.8 mm, 25 parts (15 on the bottom side), 25 nets.
